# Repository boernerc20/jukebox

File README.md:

# UNDER CONSTRUCTION

Electronics are finished and ready for jukebox enclosure:

Routing on back of perf-board:

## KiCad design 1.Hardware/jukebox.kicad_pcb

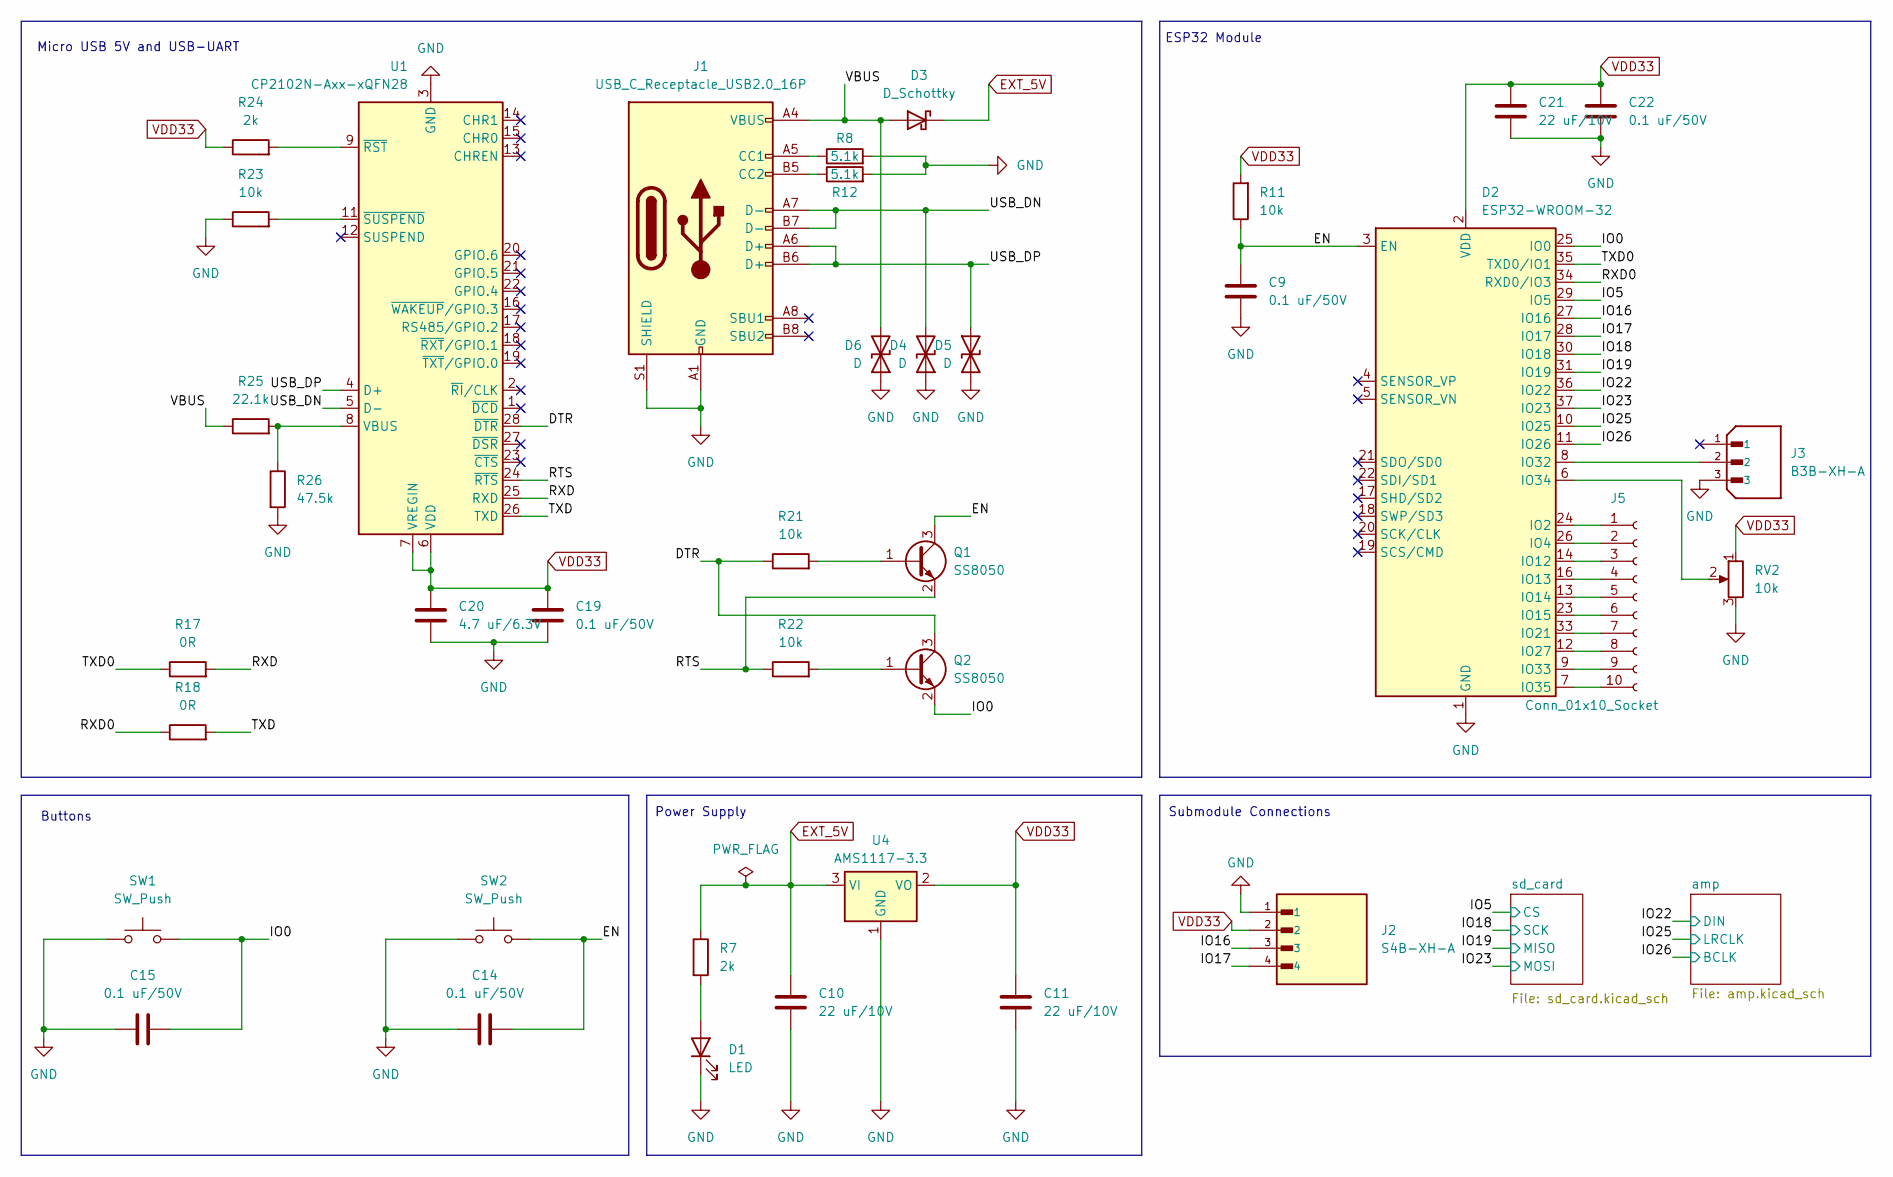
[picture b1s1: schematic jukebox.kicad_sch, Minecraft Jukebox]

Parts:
C9, C14, C15, C19, C22: 0.1 uF/50V; C_0603_1608Metric_Pad1.08x0.95mm_HandSolder
C10, C11, C21: 22 uF/10V; C_0603_1608Metric_Pad1.08x0.95mm_HandSolder
C20: 4.7 uF/6.3V; C_0603_1608Metric_Pad1.08x0.95mm_HandSolder
D1: LED; LED_0603_1608Metric_Pad1.05x0.95mm_HandSolder
D2: ESP32-WROOM-32
D3: D_Schottky; D_SOD-323F
D4, D5, D6: D; D_SOD-523
J1: USB_C_Receptacle_USB2.0_16P; USB_C_Receptacle_GCT_USB4105-xx-A_16P_TopMnt_Horizontal
J2: S4B-XH-A; JST_S4B-XH-A; DigiKey_Part_Number 455-2243-ND
J3: B3B-XH-A; JST_B3B-XH-A; PARTREV 7/4/21
J5: Conn_01x10_Socket; PinHeader_1x10_P2.54mm_Vertical
Q1, Q2: SS8050; SOT-23
R7, R24: 2k; R_0603_1608Metric_Pad0.98x0.95mm_HandSolder
R8, R12: 5.1k; R_0603_1608Metric_Pad0.98x0.95mm_HandSolder
R11, R21, R22, R23: 10k; R_0603_1608Metric_Pad0.98x0.95mm_HandSolder
R17, R18: 0R; R_0603_1608Metric_Pad0.98x0.95mm_HandSolder
R25: 22.1k; R_0603_1608Metric_Pad0.98x0.95mm_HandSolder
R26: 47.5k; R_0603_1608Metric_Pad0.98x0.95mm_HandSolder
RV2: 10k; TRIM_3306K-1-202
SW1, SW2: SW_Push; SW_SPST_B3U-1100P
U1: CP2102N-Axx-xQFN28; QFN-28-1EP_5x5mm_P0.5mm_EP3.35x3.35mm
U4: AMS1117-3.3; SOT-223-3_TabPin2

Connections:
/DTR: Q2.3 (C), R21.1, U1.28 (~DTR)
/EN: C9.1, C14.2, D2.3 (EN), Q1.3 (C), R11.1, SW2.2
/IO0: C15.2, D2.25 (IO0), Q2.2 (E), SW1.2
/IO5: D2.29 (IO5); also elsewhere on the board
/IO16: D2.27 (IO16), J2.3
/IO17: D2.28 (IO17), J2.4
/IO18: D2.30 (IO18); also elsewhere on the board
/IO19: D2.31 (IO19); also elsewhere on the board
/IO22: D2.36 (IO22); also elsewhere on the board
/IO23: D2.37 (IO23); also elsewhere on the board
/IO25: D2.10 (IO25); also elsewhere on the board
/IO26: D2.11 (IO26); also elsewhere on the board
/RTS: Q1.2 (E), R22.1, U1.24 (~RTS)
/RXD: R17.2, U1.25 (RXD)
/RXD0: D2.34 (RXD0/IO3), R18.1
/TXD: R18.2, U1.26 (TXD)
/TXD0: D2.35 (TXD0/IO1), R17.1
/USB_DN: D4.2 (A2), J1.A7 (D-), J1.B7 (D-), U1.5 (D-)
/USB_DP: D5.1 (A1), J1.A6 (D+), J1.B6 (D+), U1.4 (D+)
/VBUS: D3.2 (A), D6.2 (A2), J1.A4 (VBUS), J1.A9 (VBUS), J1.B4 (VBUS), J1.B9 (VBUS), R25.1
EXT_5V: C10.1, D3.1 (K), R7.1, U4.3 (VI)
GND: C9.2, C10.2, C11.2, C14.1, C15.1, C19.2, C20.2, C21.2, C22.2, D1.1 (K), D2.1 (GND), D2.15 (GND), D2.38 (GND), D2.39 (GND), D4.1 (A1), D5.2 (A2), D6.1 (A1), J1.A1 (GND), J1.A12 (GND), J1.B1 (GND), J1.B12 (GND), J1.S1 (SHIELD), J2.1, J3.3, R8.2, R12.2, R23.1, R26.2, RV2.3, SW1.1, SW2.1, U1.3 (GND), U1.29 (GND), U4.1 (GND); also elsewhere on the board
unnamed: D1.2 (A), R7.2
unnamed: D2.24 (IO2), J5.1
unnamed: D2.26 (IO4), J5.2
unnamed: D2.14 (IO12), J5.3
unnamed: D2.16 (IO13), J5.4
unnamed: D2.13 (IO14), J5.5
unnamed: D2.23 (IO15), J5.6
unnamed: D2.33 (IO21), J5.7
unnamed: D2.12 (IO27), J5.8
unnamed: D2.8 (IO32), J3.2
unnamed: D2.9 (IO33), J5.9
unnamed: D2.6 (IO34), RV2.2
unnamed: D2.7 (IO35), J5.10
unnamed: J1.A5 (CC1), R8.1
unnamed: J1.B5 (CC2), R12.1
unnamed: Q1.1 (B), R21.2
unnamed: Q2.1 (B), R22.2
unnamed: R25.2, R26.1, U1.8 (VBUS)
unnamed: R24.2, U1.9 (~RST)
unnamed: R23.2, U1.11 (~SUSPEND)
VDD33: C11.1, C19.1, C20.1, C21.1, C22.1, D2.2 (VDD), J2.2, R11.2, R24.1, RV2.1, U1.6 (VDD), U1.7 (VREGIN), U4.2 (VO); also elsewhere on the board

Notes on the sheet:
Power Supply
Buttons
ESP32 Module
Submodule Connections
Micro USB 5V and USB-UART

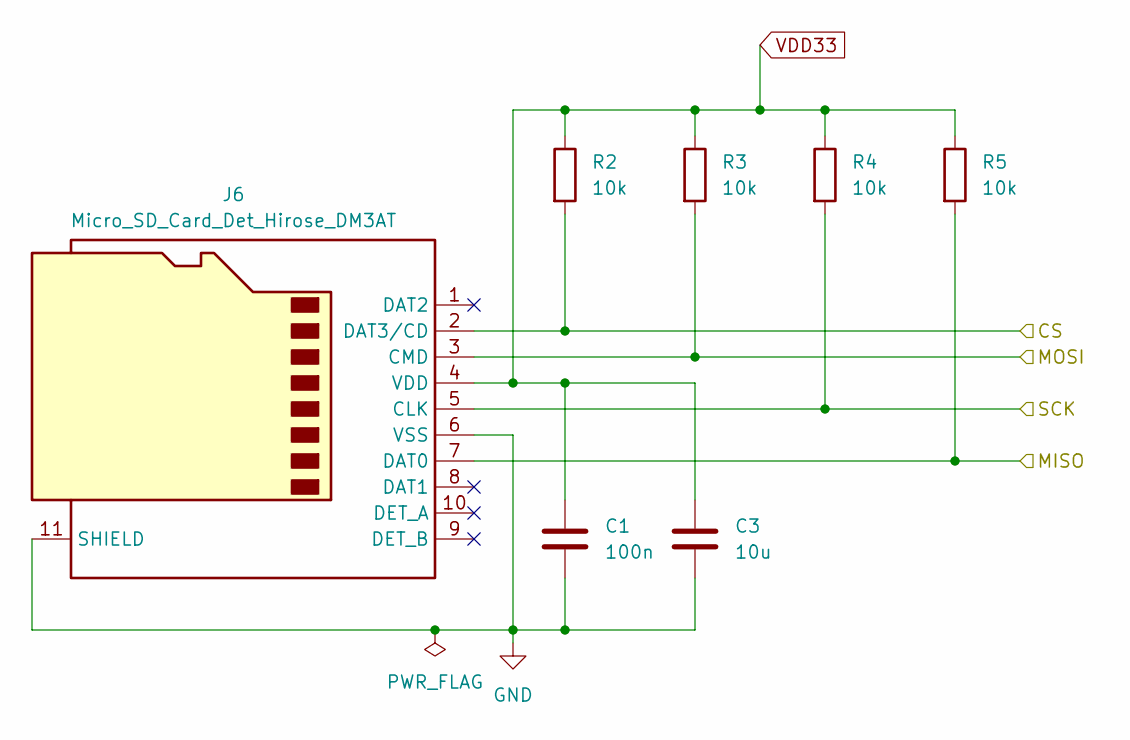
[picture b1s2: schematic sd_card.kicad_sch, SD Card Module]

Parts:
C1: 100n; C_0603_1608Metric_Pad1.08x0.95mm_HandSolder
C3: 10u; C_0603_1608Metric_Pad1.08x0.95mm_HandSolder
J6: Micro_SD_Card_Det_Hirose_DM3AT
R2, R3, R4, R5: 10k; R_0603_1608Metric_Pad0.98x0.95mm_HandSolder

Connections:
/IO5: J6.2 (DAT3/CD), R2.2; also elsewhere on the board
/IO18: J6.5 (CLK), R4.2; also elsewhere on the board
/IO19: J6.7 (DAT0), R5.2; also elsewhere on the board
/IO23: J6.3 (CMD), R3.2; also elsewhere on the board
GND: C1.2, C3.2, J6.6 (VSS), J6.11 (SHIELD); also elsewhere on the board
VDD33: C1.1, C3.1, J6.4 (VDD), R2.1, R3.1, R4.1, R5.1; also elsewhere on the board

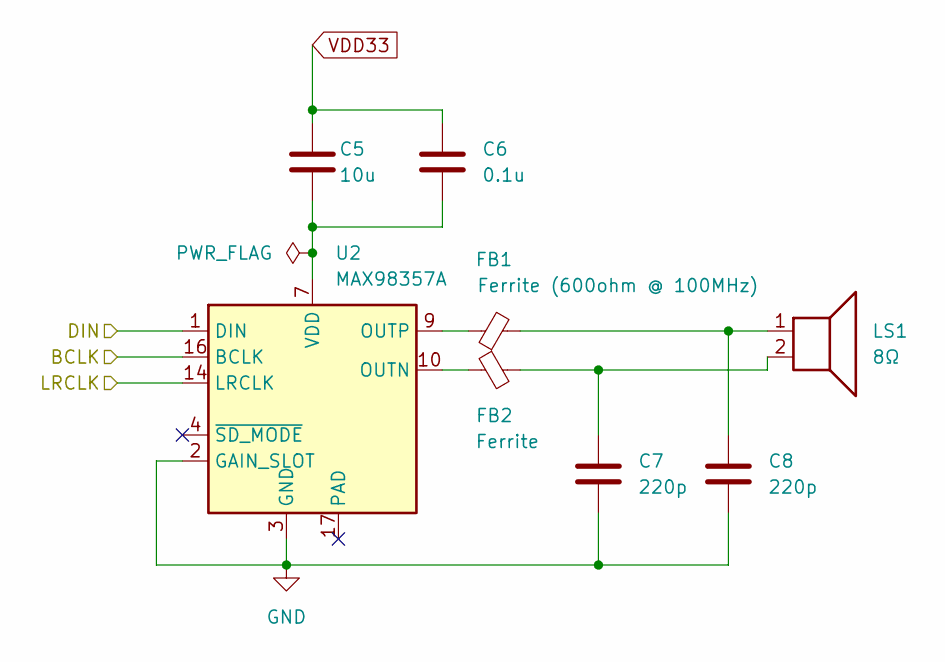
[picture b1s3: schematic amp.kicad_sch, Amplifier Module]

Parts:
C5: 10u; C_0603_1608Metric_Pad1.08x0.95mm_HandSolder
C6: 0.1u; C_0603_1608Metric_Pad1.08x0.95mm_HandSolder
C7, C8: 220p; C_0603_1608Metric_Pad1.08x0.95mm_HandSolder
FB1: Ferrite (600ohm @ 100MHz); BEADC2012X105N
FB2: Ferrite; BEADC2012X105N
LS1: 8Ω; TerminalBlock_Phoenix_MPT-0,5-2-2.54_1x02_P2.54mm_Horizontal
U2: MAX98357A; TQFN-16-1EP_3x3mm_P0.5mm_EP1.23x1.23mm

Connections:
/IO22: U2.1 (DIN); also elsewhere on the board
/IO25: U2.14 (LRCLK); also elsewhere on the board
/IO26: U2.16 (BCLK); also elsewhere on the board
GND: C7.2, C8.2, U2.2 (GAIN_SLOT), U2.3 (GND), U2.11 (GND), U2.15 (GND); also elsewhere on the board
unnamed: C5.2, C6.2, U2.7 (VDD), U2.8 (VDD)
unnamed: C7.1, FB2.2, LS1.2
unnamed: C8.1, FB1.2, LS1.1
unnamed: FB2.1, U2.10 (OUTN)
unnamed: FB1.1, U2.9 (OUTP)
VDD33: C5.1, C6.1; also elsewhere on the board

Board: 2 copper layers, 52 parts (0 on the bottom side), 48 nets, no tracks yet.

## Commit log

2025-07-21 intial commit of kicad project
2025-07-21 power and sd added
2025-07-22 amp and sd sheets revision 1
2025-07-22 rfid revision 1 sch
2025-07-23 adding firmware for prototyping
2025-07-23 fixed lib problem
2025-07-23 pcb update
2025-07-23 laptop push 7-23
2025-07-23 audio working with volume
2025-07-23 audio and volume control working
2025-07-24 rfid ready to test
2025-07-24 rfid working and tag-to-CD
2025-07-27 main state machine created, multiple tags working
2025-07-29 restructuring folders
2025-07-29 restructuring
2025-07-29 rename firmware
2025-07-29 adding two folders
2025-07-29 changed to usb c
2025-07-30 10 CDs added and working
2025-08-08 updated schematic to match demo
2025-08-11 ready for routing/placement
2025-08-15 transferring to laptop
2025-08-22 electronics done
2025-08-22 update images
2025-08-22 Update README with electronics and routing images
    Added images and descriptions for electronics and routing.
2025-08-25 jukebox V1.0
2025-08-25 V1.1 jukebox
2025-08-25 V1.1 enclosure
2025-08-25 fixed error
2025-08-25 moved sd up
